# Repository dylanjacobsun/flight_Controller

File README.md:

# Objective
Purpose of this project is to develop an autonomous flying wing that will fly waypoint
missions. I am designing and building everything myself including electrical schematics,
PCB layout, component assembly, and system testing. The flight controller will be running 
on FreeRTOS and will be programmed in C.

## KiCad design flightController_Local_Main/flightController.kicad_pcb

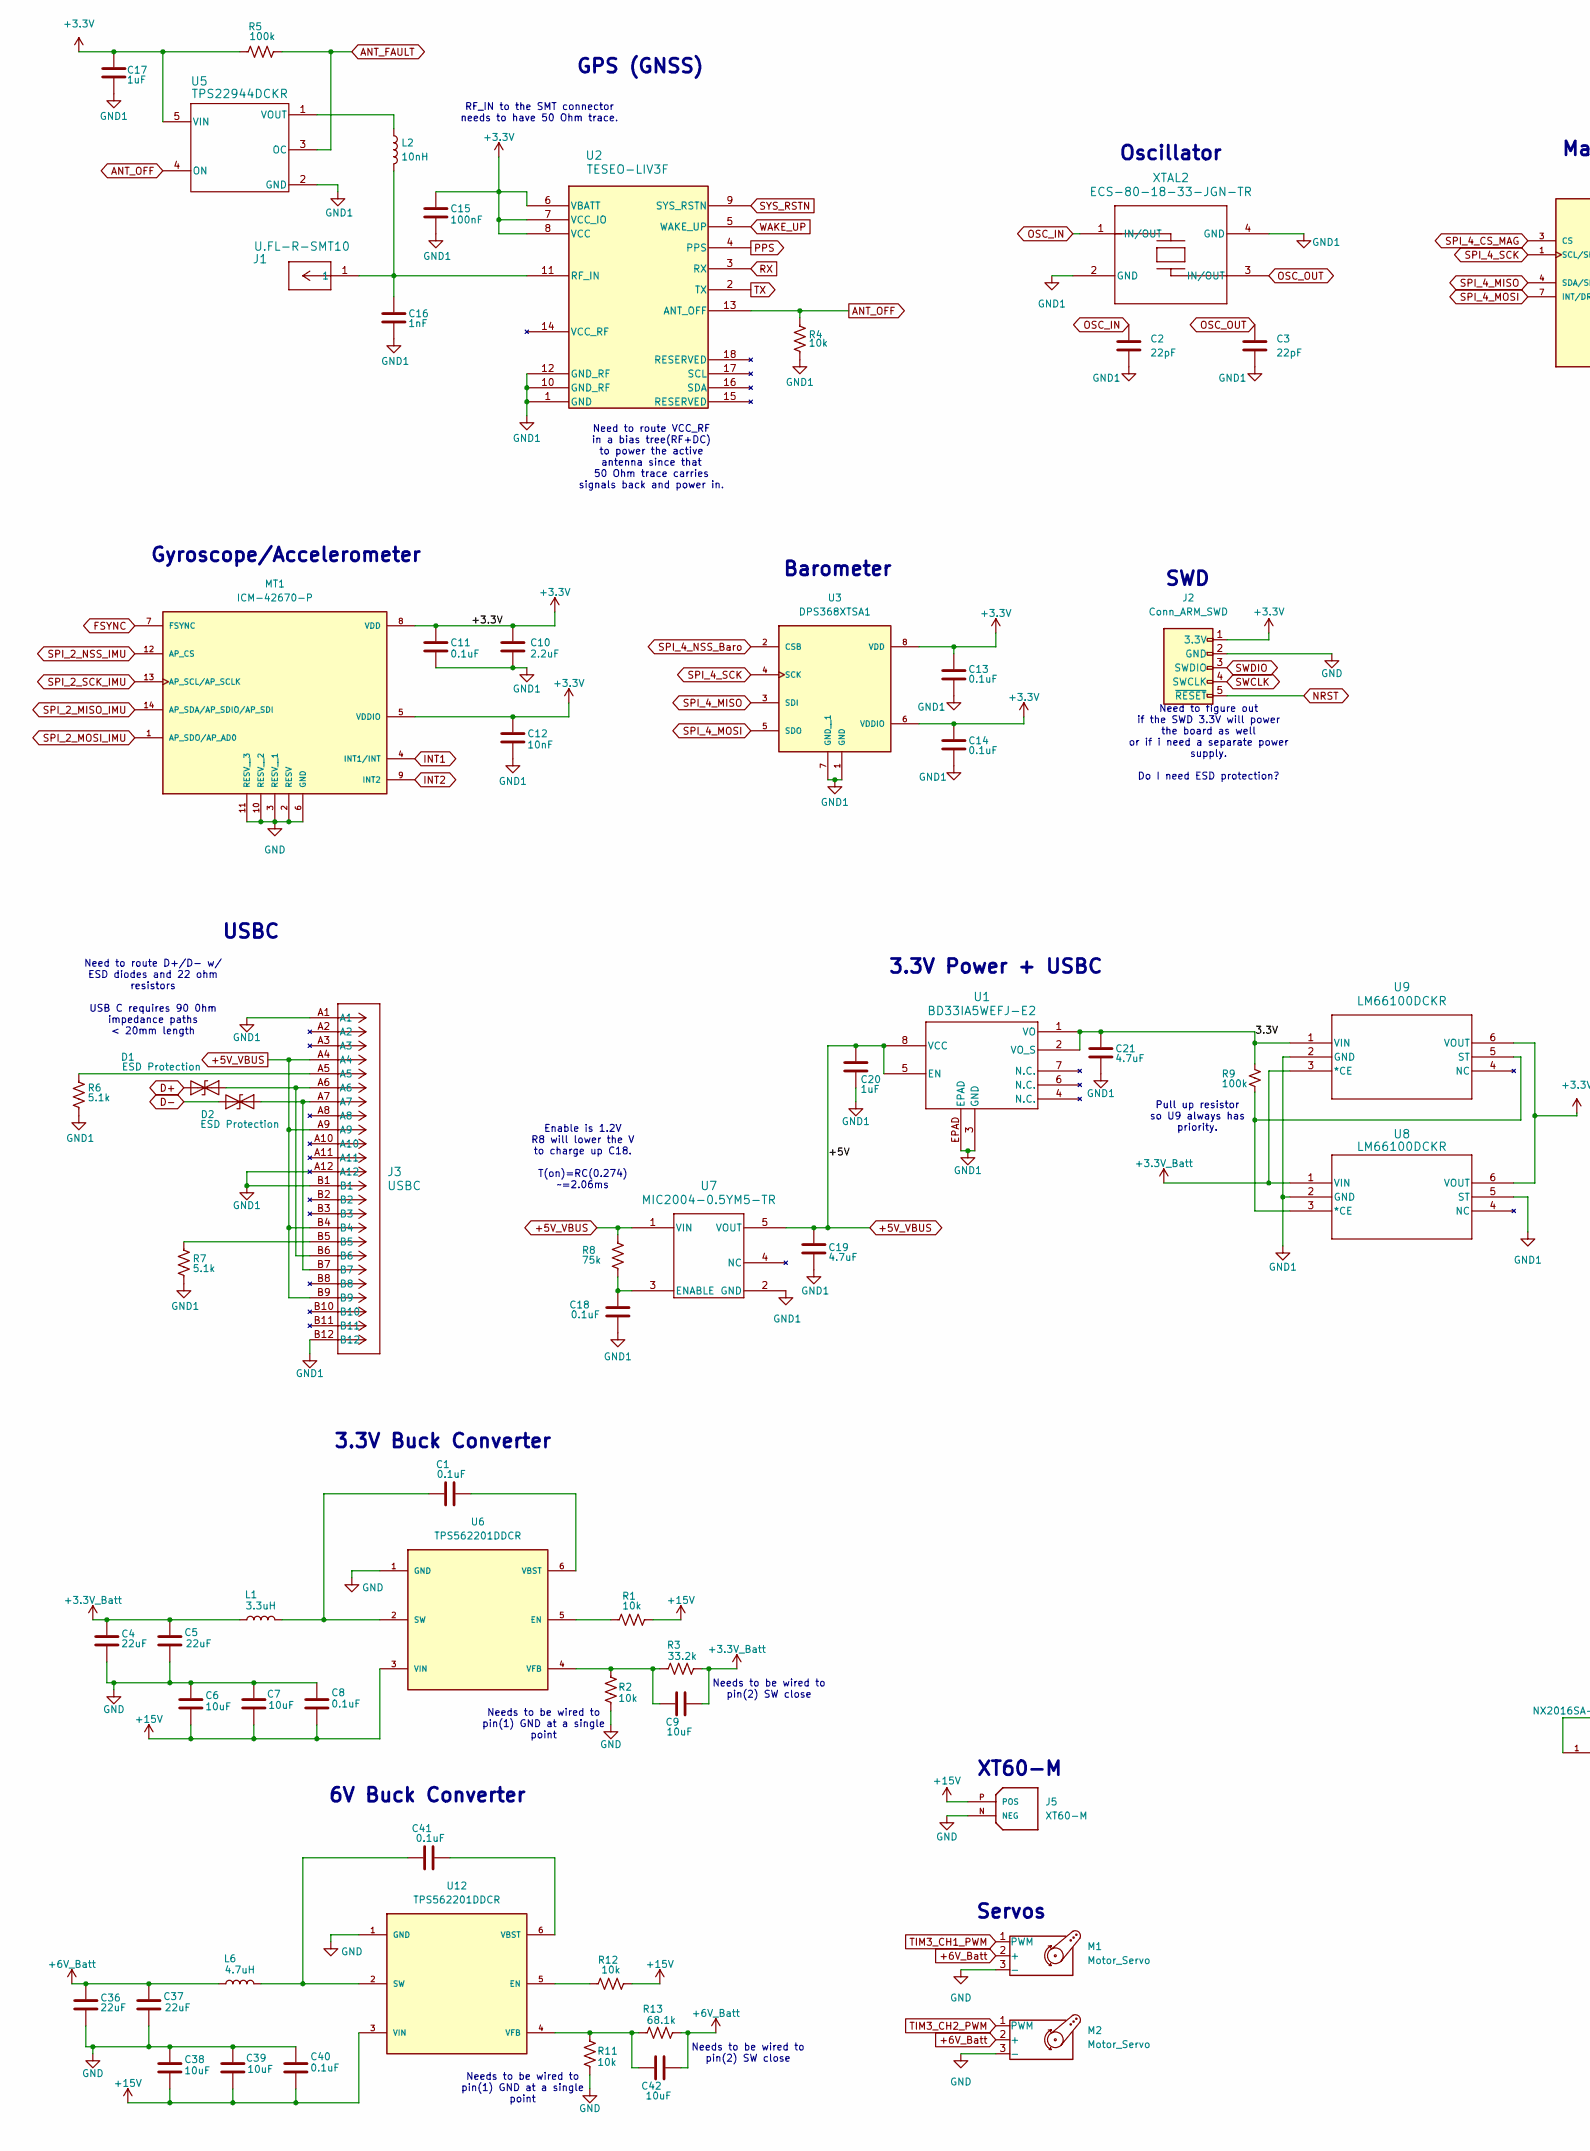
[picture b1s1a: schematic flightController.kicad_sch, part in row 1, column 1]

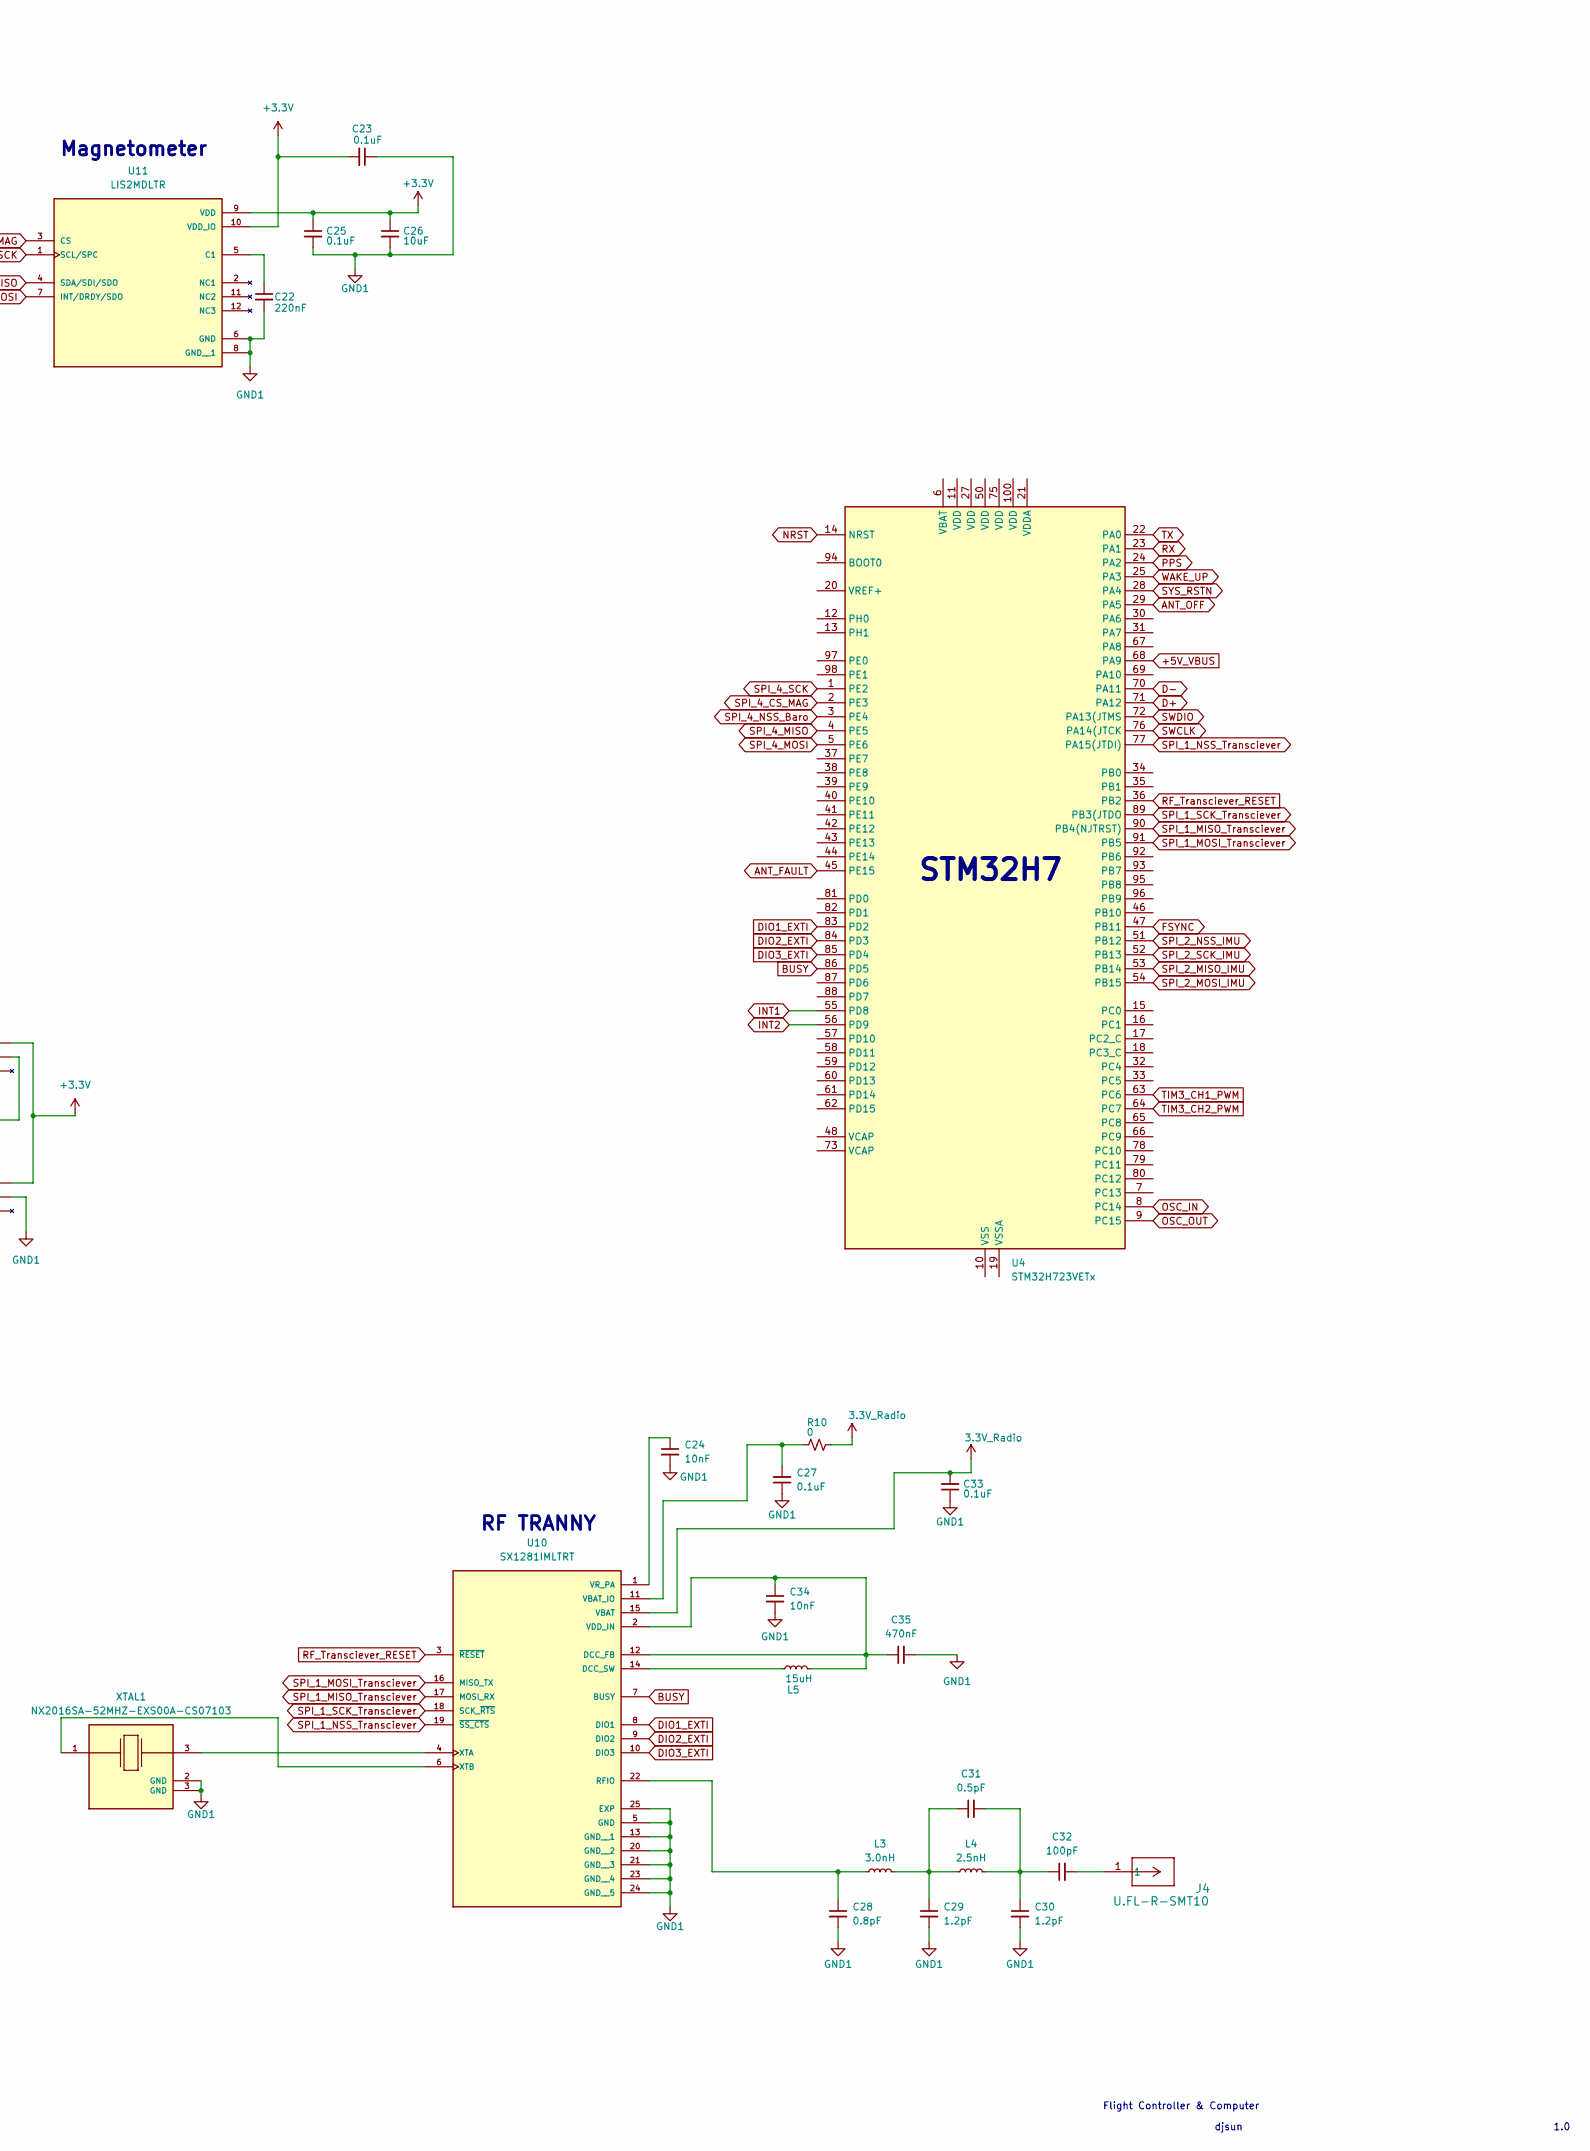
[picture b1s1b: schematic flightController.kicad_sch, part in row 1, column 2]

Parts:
C1, C8, C11, C13, C14, C18, C23, C25, C27, C33, C40, C41: 0.1uF; C_0603_1608Metric
C2, C3: 22pF; C_0603_1608Metric
C4, C5, C36, C37: 22uF; C_0805_2012Metric
C6, C7, C26, C38, C39: 10uF; C_1206_3216Metric
C9, C42: 10uF; C_0805_2012Metric
C10: 2.2uF; C_0603_1608Metric
C12, C24, C34: 10nF; C_0603_1608Metric
C15: 100nF; C_0603_1608Metric
C16: 1nF; C_0603_1608Metric
C17, C20: 1uF; C_0603_1608Metric
C19, C21: 4.7uF; C_0603_1608Metric
C22: 220nF; C_0603_1608Metric
C28: 0.8pF; C_0603_1608Metric
C29, C30: 1.2pF; C_0603_1608Metric
C31: 0.5pF; C_0603_1608Metric
C32: 100pF; C_0603_1608Metric
C35: 470nF; C_0603_1608Metric
D1, D2: ESD Protection; ESD_6V (3)
J1, J4: U.FL-R-SMT10; U.FL_CONN_v.UL
J2: Conn_ARM_SWD; PinHeader_1x05_P1.27mm_Vertical
J3: USBC; USB_C_Receptacle_Molex_105450-0101
J5: XT60-M; PARTREV V1.2
L1: 3.3uH; 3.3uH_3.94A
L2: 10nH; 10nH_Inductor
L3: 3.0nH; 3.0nH_Inductor
L4: 2.5nH; 3.0nH_Inductor
L5: 15uH; 15uH_Inductor
L6: 4.7uH; 4.7uH_7.18A
M1, M2: Motor_Servo; JST_XH_B3B-XH-AM_1x03_P2.50mm_Vertical
MT1: ICM-42670-P; XDCR_ICM-42670-P; PARTREV 1.1
R1, R2, R4, R11, R12: 10k; R_0603_1608Metric
R3: 33.2k; R_0603_1608Metric
R5, R9: 100k; R_0603_1608Metric
R6, R7: 5.1k; R_0603_1608Metric
R8: 75k; R_0603_1608Metric
R10: 0; R_0603_1608Metric
R13: 68.1k; R_0603_1608Metric
U1: BD33IA5WEFJ-E2; 3.3V-LDO (2)
U2: TESEO-LIV3F
U3: DPS368XTSA1; XDCR_DPS368XTSA1
U4: STM32H723VETx; LQFP-100_14x14mm_P0.5mm
U5: TPS22944DCKR; TPS22944 (2)
U6, U12: TPS562201DDCR; 3.3Buck; PARTREV A
U7: MIC2004-0.5YM5-TR; Current-Limiter-500mA (1)
U8, U9: LM66100DCKR; Ideal_diode (2)
U10: SX1281IMLTRT; XCVR_SX1281IMLTRT; PARTREV 3.3
U11: LIS2MDLTR; Magnetometer; PARTREV Rev 5
XTAL1: NX2016SA-52MHZ-EXS00A-CS07103; Tranny_OSC; PARTREV N/A
XTAL2: ECS-80-18-33-JGN-TR; Crystal

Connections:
3.3V_Radio: C33.2, R10.1, U10.15 (VBAT)
+3.3V: C10.1, C11.1, C12.1, C13.1, C14.1, C15.1, C17.1, C23.2, C25.1, C26.1, J2.1 (3.3V), MT1.5 (VDDIO), MT1.8 (VDD), R5.2, U2.6 (VBATT), U2.7 (VCC_IO), U2.8 (VCC), U3.6 (VDDIO), U3.8 (VDD), U5.5 (VIN), U8.6 (VOUT), U9.6 (VOUT), U11.9 (VDD), U11.10 (VDD_IO)
+3.3V_Batt: C4.1, C5.1, C9.2, L1.1, R3.1, U8.1 (VIN), U9.3 (*CE)
+5V_VBUS: C19.1, C20.1, J3.A4, J3.A9, J3.B4, J3.B9, R8.1, U1.5 (EN), U1.8 (VCC), U4.68 (PA9), U7.1 (VIN), U7.5 (VOUT)
+6V_Batt: C36.1, C37.1, C42.2, L6.1, M1.2 (+), M2.2 (+), R13.1
+15V: C6.2, C7.2, C8.2, C38.2, C39.2, C40.2, J5.P (POS), R1.2, R12.2, U6.3 (VIN), U12.3 (VIN)
/3.3V: C21.1, R9.1, U1.1 (VO), U1.2 (VO_S), U9.1 (VIN)
ANT_FAULT: R5.1, U4.45 (PE15), U5.3 (OC)
ANT_OFF: R4.1, U2.13 (ANT_OFF), U4.29 (PA5), U5.4 (ON)
BUSY: U4.86 (PD5), U10.7 (BUSY)
D+: D1.1 (A1), U4.71 (PA12)
D-: D2.1 (A1), U4.70 (PA11)
DIO1_EXTI: U4.83 (PD2), U10.8 (DIO1)
DIO2_EXTI: U4.84 (PD3), U10.9 (DIO2)
DIO3_EXTI: U4.85 (PD4), U10.10 (DIO3)
FSYNC: MT1.7 (FSYNC), U4.47 (PB11)
GND: C4.2, C5.2, C6.1, C7.1, C8.1, C36.2, C37.2, C38.1, C39.1, C40.1, J2.2 (GND), J5.N (NEG), M1.3 (-), M2.3 (-), MT1.2 (RESV), MT1.3 (RESV__1), MT1.6 (GND), MT1.10 (RESV__2), MT1.11 (RESV__3), R2.1, R11.1, U6.1 (GND), U12.1 (GND)
INT1: MT1.4 (INT1/INT), U4.55 (PD8)
INT2: MT1.9 (INT2), U4.56 (PD9)
NRST: J2.5 (~RESET), U4.14 (NRST)
unnamed: C29.1, C31.1, L3.2, L4.1
unnamed: C30.1, C31.2, C32.1, L4.2
unnamed: C32.2, J4.1
unnamed: D1.2 (A2), J3.A6, J3.B6
unnamed: D2.2 (A2), J3.A7, J3.B7
unnamed: J3.A5, R6.1
unnamed: J3.B5, R7.1
unnamed: C16.1, J1.1, L2.2, U2.11 (RF_IN)
unnamed: U4.10 (VSS), U4.26 (VSS), U4.49 (VSS), U4.74 (VSS), U4.99 (VSS)
unnamed: L2.1, U5.1 (VOUT)
unnamed: R1.1, U6.5 (EN)
unnamed: C1.1, L1.2, U6.2 (SW)
unnamed: C1.2, U6.6 (VBST)
unnamed: C9.1, R2.2, R3.2, U6.4 (VFB)
unnamed: C18.1, R8.2, U7.3 (ENABLE)
unnamed: R9.2, U8.3 (*CE), U9.5 (ST)
unnamed: C34.1, C35.1, L5.2, U10.2 (VDD_IN), U10.12 (DCC_FB)
unnamed: L5.1, U10.14 (DCC_SW)
unnamed: C28.1, L3.1, U10.22 (RFIO)
unnamed: C27.2, R10.2, U10.11 (VBAT_IO)
unnamed: C24.1, U10.1 (VR_PA)
unnamed: U10.6 (XTB), XTAL1.1
unnamed: C22.1, U11.5 (C1)
unnamed: R12.1, U12.5 (EN)
unnamed: C41.1, L6.2, U12.2 (SW)
unnamed: C41.2, U12.6 (VBST)
unnamed: C42.1, R11.2, R13.2, U12.4 (VFB)
OSC_IN: C2.2, U4.8 (PC14), XTAL2.1 (IN/OUT)
OSC_OUT: C3.2, U4.9 (PC15), XTAL2.3 (IN/OUT)
PPS: U2.4 (PPS), U4.24 (PA2)
RF_Transciever_RESET: U4.36 (PB2), U10.3 (~RESET)
RX: U2.3 (RX), U4.23 (PA1)
SPI_1_MISO_Transciever: U4.90 (PB4(NJTRST)), U10.17 (MOSI_RX)
SPI_1_MOSI_Transciever: U4.91 (PB5), U10.16 (MISO_TX)
SPI_1_NSS_Transciever: U4.77 (PA15(JTDI)), U10.19 (~SS_CTS)
SPI_1_SCK_Transciever: U4.89 (PB3(JTDO), U10.18 (SCK_~RTS)
SPI_2_MISO_IMU: MT1.14 (AP_SDA/AP_SDIO/AP_SDI), U4.53 (PB14)
SPI_2_MOSI_IMU: MT1.1 (AP_SDO/AP_AD0), U4.54 (PB15)
SPI_2_NSS_IMU: MT1.12 (AP_CS), U4.51 (PB12)
SPI_2_SCK_IMU: MT1.13 (AP_SCL/AP_SCLK), U4.52 (PB13)
SPI_4_CS_MAG: U4.2 (PE3), U11.3 (CS)
SPI_4_MISO: U3.3 (SDI), U4.4 (PE5), U11.4 (SDA/SDI/SDO)
SPI_4_MOSI: U3.5 (SDO), U4.5 (PE6), U11.7 (INT/DRDY/SDO)
SPI_4_NSS_Baro: U3.2 (CSB), U4.3 (PE4)
SPI_4_SCK: U3.4 (SCK), U4.1 (PE2), U11.1 (SCL/SPC)
SWCLK: J2.4 (SWCLK), U4.76 (PA14(JTCK)
SWDIO: J2.3 (SWDIO), U4.72 (PA13(JTMS)
SYS_RSTN: U2.9 (SYS_RSTN), U4.28 (PA4)
TIM3_CH1_PWM: M1.1 (PWM), U4.63 (PC6)
TIM3_CH2_PWM: M2.1 (PWM), U4.64 (PC7)
TX: U2.2 (TX), U4.22 (PA0)
WAKE_UP: U2.5 (WAKE_UP), U4.25 (PA3)

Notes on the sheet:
Gyroscope/Accelerometer
6V Buck Converter
Pull up resistor so U9 always has priority.
STM32H7
Flight Controller & Computer
Magnetometer
Need to route D+/D- w/ ESD diodes and 22 ohm resistors USB C requires 90 0hm impedance paths < 20mm length
1.0
Needs to be wired to pin(1) GND at a single point
Need to figure out if the SWD 3.3V will power the board as well or if i need a separate power supply. Do I need ESD protection?
djsun
Needs to be wired to pin(2) SW close
3.3V Buck Converter
XT60-M
Servos
USBC
GPS (GNSS)
RF TRANNY
Barometer
RF_IN to the SMT connector needs to have 50 Ohm trace.
Need to route VCC_RF in a bias tree(RF+DC) to power the active antenna since that 50 Ohm trace carries signals back and power in.
Enable is 1.2V R8 will lower the V to charge up C18. T(on)=RC(0.274) ~=2.06ms
SWD
Oscillator
3.3V Power + USBC

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
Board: 2 copper layers, 85 parts (0 on the bottom side), 73 nets, no tracks yet.

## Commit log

2025-04-16 Adding Initial Folders for flight controller schematic
2025-04-16 removing discord and whatsapp exe
2025-04-16 Ignoring executable files
2025-04-16 Changing Componenets_local_main to Components
2025-04-17 adding footprints and models for buck
2025-04-18 Adding caps to IMU and Barometer
2025-04-24 Making changes to GPS
2025-05-02 Adding GPS passives and SWD
2025-06-03 Adding updates
2025-06-05 Adding the magnetometer and changing SPI pin outs
2025-06-25 Adding all step files and footprints
